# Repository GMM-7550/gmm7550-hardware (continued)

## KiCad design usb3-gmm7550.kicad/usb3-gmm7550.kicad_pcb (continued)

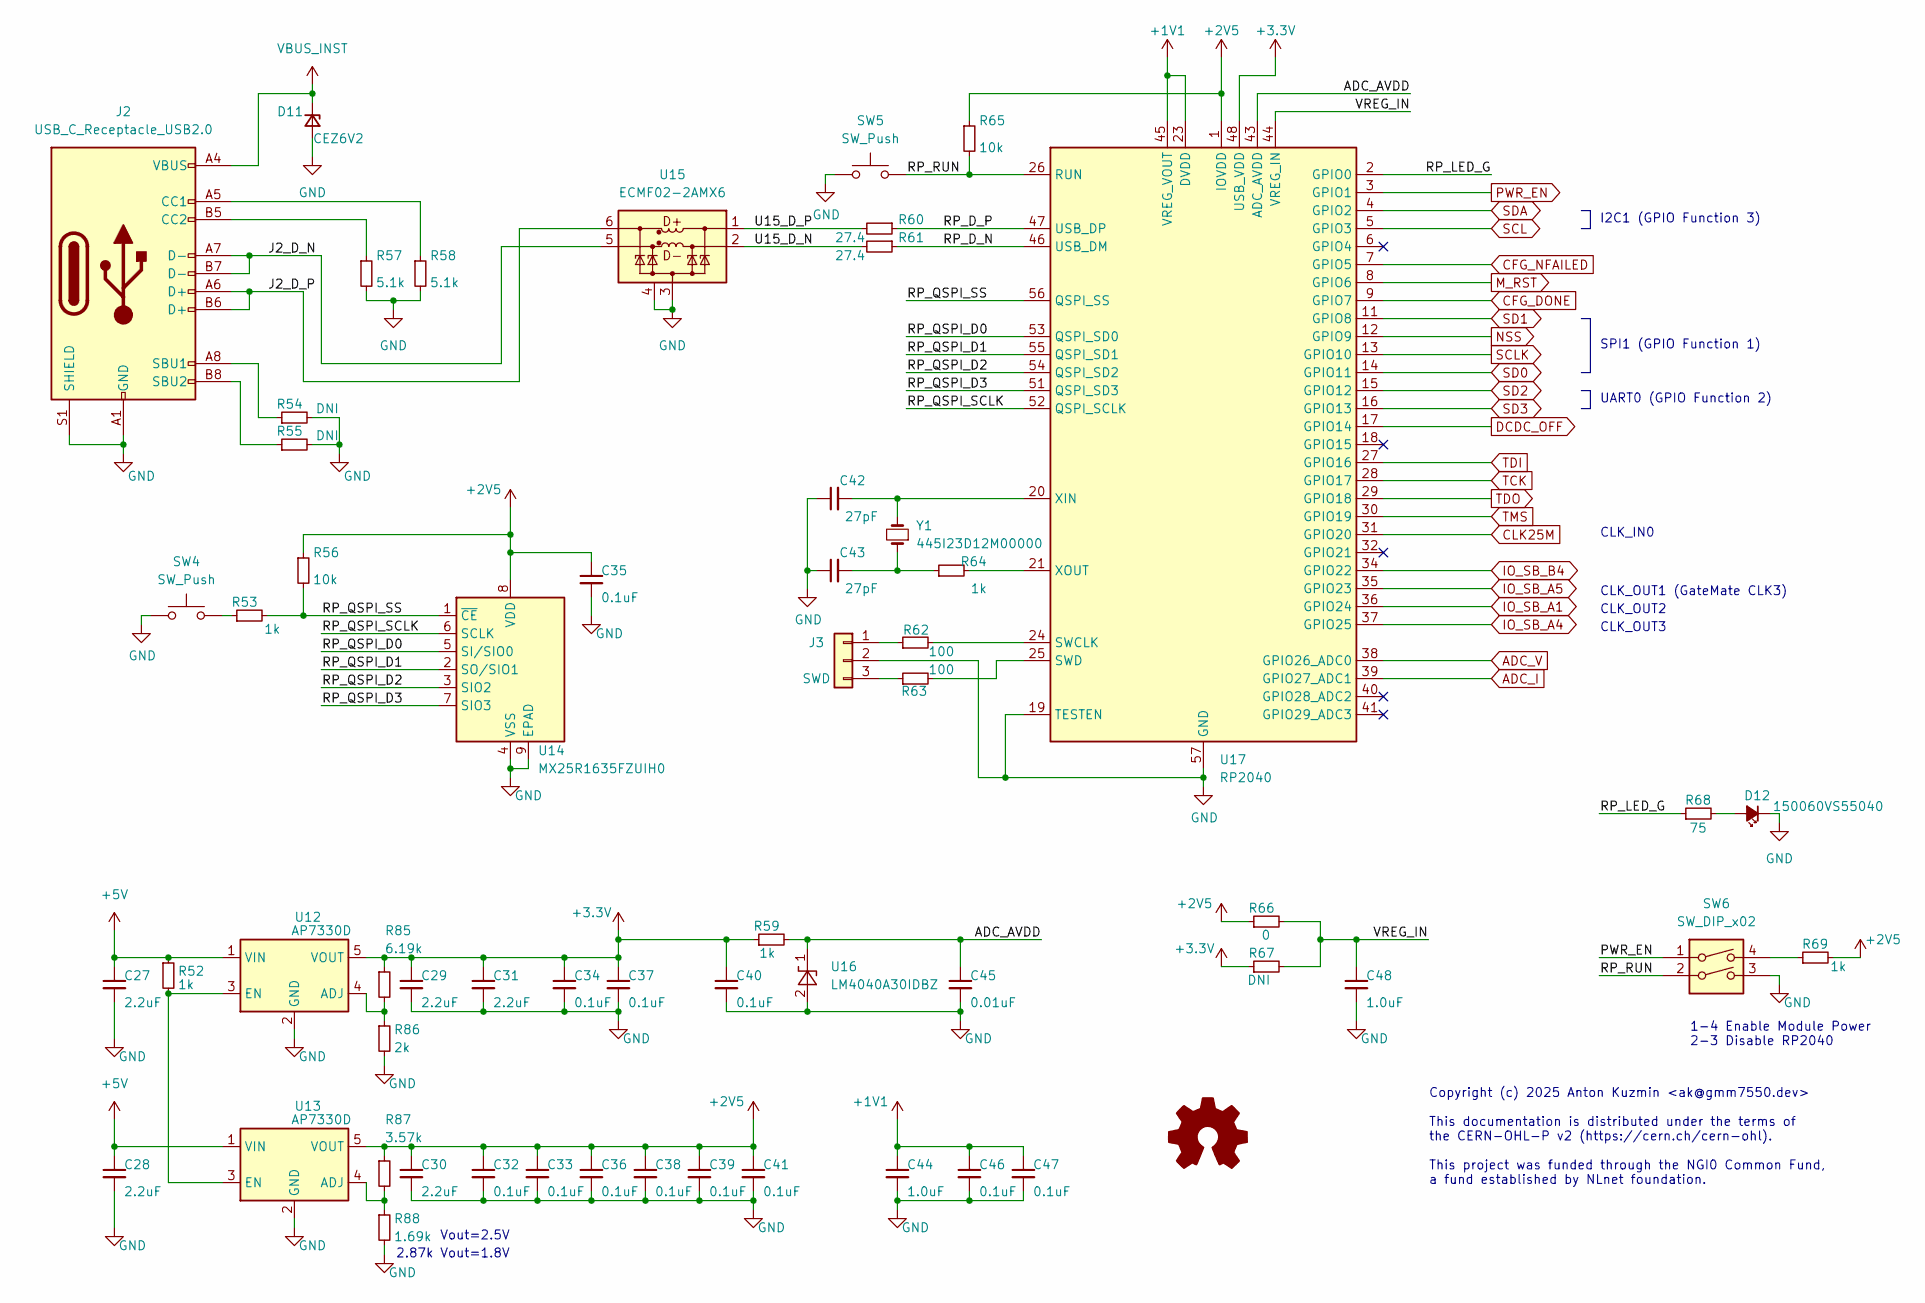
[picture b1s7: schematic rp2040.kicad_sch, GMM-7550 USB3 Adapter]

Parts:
C27, C28, C29, C30, C31: 2.2uF; C_0603_1608Metric
C32, C33, C34, C35, C36, C37, C38, C39, C40, C41, C46, C47: 0.1uF; C_0402_1005Metric
C42, C43: 27pF; C_0402_1005Metric
C44, C48: 1.0uF; C_0402_1005Metric
C45: 0.01uF; C_0402_1005Metric
D11: CEZ6V2; D_SOD-523
D12: 150060VS55040; LED_0603_1608Metric
J2: USB_C_Receptacle_USB2.0; USB_C_Receptacle_GCT_USB4105-xx-A_16P_TopMnt_Horizontal
J3: SWD; JST_SH_SM03B-SRSS-TB_1x03-1MP_P1.00mm_Horizontal
R52, R53, R59, R64, R69: 1k; R_0402_1005Metric
R54, R55, R67: DNI; R_0402_1005Metric
R56, R65: 10k; R_0402_1005Metric
R57, R58: 5.1k; R_0402_1005Metric
R60, R61: 27.4; R_0402_1005Metric
R62, R63: 100; R_0402_1005Metric
R66: 0; R_0402_1005Metric
R68: 75; R_0402_1005Metric
R85: 6.19k; R_0402_1005Metric
R86: 2k; R_0402_1005Metric
R87: 3.57k; R_0402_1005Metric
R88: 1.69k; R_0402_1005Metric
SW4, SW5: SW_Push; SW_SPST_PTS810
SW6: SW_DIP_x02; SW_DIP_SPSTx02_Slide_Omron_A6H-2101_W6.15mm_P1.27mm
U12, U13: AP7330D; SOT-23-5
U14: MX25R1635FZUIH0; Winbond_USON-8-1EP_3x2mm_P0.5mm_EP0.2x1.6mm
U15: ECMF02-2AMX6; ST_UQFN-6L_1.5x1.7mm_P0.5mm
U16: LM4040A30IDBZ; SOT-23
U17: RP2040; QFN-56-1EP_7x7mm_P0.4mm_EP3.2x3.2mm
Y1: 445I23D12M00000; Crystal_SMD_5032-2Pin_5.0x3.2mm

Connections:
+1V1: C44.1, C46.1, C47.1, U17.23 (DVDD), U17.45 (VREG_VOUT), U17.50 (DVDD)
+2V5: C30.1, C32.1, C33.1, C35.1, C36.1, C38.1, C39.1, C41.1, R56.1, R65.1, R66.1, R69.2, R87.1, U13.5 (VOUT), U14.8 (VDD), U17.1 (IOVDD), U17.10 (IOVDD), U17.22 (IOVDD), U17.33 (IOVDD), U17.42 (IOVDD), U17.49 (IOVDD)
+3.3V: C29.1, C31.1, C34.1, C37.1, C40.1, R59.1, R67.1, R85.1, U12.5 (VOUT), U17.48 (USB_VDD); also elsewhere on the board
+5V: C27.1, C28.1, R52.1, U12.1 (VIN), U13.1 (VIN); also elsewhere on the board
/RP2040/ADC_AVDD: C45.1, R59.2, U16.1 (K), U17.43 (ADC_AVDD)
/RP2040/J2_D_N: J2.A7 (D-), J2.B7 (D-), U15.5 (D-_out)
/RP2040/J2_D_P: J2.A6 (D+), J2.B6 (D+), U15.6 (D+_out)
/RP2040/RP_D_N: R61.1, U17.46 (USB_DM)
/RP2040/RP_D_P: R60.1, U17.47 (USB_DP)
/RP2040/RP_LED_G: R68.1, U17.2 (GPIO0)
/RP2040/RP_QSPI_D0: U14.5 (SI/SIO0), U17.53 (QSPI_SD0)
/RP2040/RP_QSPI_D1: U14.2 (SO/SIO1), U17.55 (QSPI_SD1)
/RP2040/RP_QSPI_D2: U14.3 (SIO2), U17.54 (QSPI_SD2)
/RP2040/RP_QSPI_D3: U14.7 (SIO3), U17.51 (QSPI_SD3)
/RP2040/RP_QSPI_SCLK: U14.6 (SCLK), U17.52 (QSPI_SCLK)
/RP2040/RP_QSPI_SS: R53.2, R56.2, U14.1 (~CE), U17.56 (QSPI_SS)
/RP2040/RP_RUN: R65.2, SW5.2, SW6.2, U17.26 (RUN)
/RP2040/U15_D_N: R61.2, U15.2 (D-_in)
/RP2040/U15_D_P: R60.2, U15.1 (D+_in)
/RP2040/VREG_IN: C48.1, R66.2, R67.2, U17.44 (VREG_IN)
ADC_I: U17.39 (GPIO27_ADC1); also elsewhere on the board
ADC_V: U17.38 (GPIO26_ADC0); also elsewhere on the board
CFG_DONE: U17.9 (GPIO7); also elsewhere on the board
CFG_NFAILED: U17.7 (GPIO5); also elsewhere on the board
CLK25M: U17.31 (GPIO20); also elsewhere on the board
DCDC_OFF: U17.17 (GPIO14); also elsewhere on the board
GND: C27.2, C28.2, C29.2, C30.2, C31.2, C32.2, C33.2, C34.2, C35.2, C36.2, C37.2, C38.2, C39.2, C40.2, C41.2, C42.1, C43.1, C44.2, C45.2, C46.2, C47.2, C48.2, D11.2 (A), D12.1 (K), J2.A1 (GND), J2.A12 (GND), J2.B1 (GND), J2.B12 (GND), J2.S1 (SHIELD), J3.2, R54.2, R55.2, R57.2, R58.2, R86.2, R88.2, SW4.1, SW5.1, SW6.3, U12.2 (GND), U13.2 (GND), U14.4 (VSS), U14.9 (EPAD), U15.3 (GND), U15.4 (NC), U16.2 (A), U17.19 (TESTEN), U17.57 (GND); also elsewhere on the board
IO_SB_A1: U17.36 (GPIO24); also elsewhere on the board
IO_SB_A4: U17.37 (GPIO25); also elsewhere on the board
IO_SB_A5: U17.35 (GPIO23); also elsewhere on the board
IO_SB_B4: U17.34 (GPIO22); also elsewhere on the board
M_RST: U17.8 (GPIO6); also elsewhere on the board
NSS: U17.12 (GPIO9); also elsewhere on the board
unnamed: C43.2, R64.1, Y1.1
unnamed: D12.2 (A), R68.2
unnamed: J2.A5 (CC1), R58.1
unnamed: J2.B5 (CC2), R57.1
unnamed: J2.A8 (SBU1), R54.1
unnamed: J2.B8 (SBU2), R55.1
unnamed: J3.1, R62.1
unnamed: J3.3, R63.1
unnamed: R53.1, SW4.2
unnamed: R69.1, SW6.4
unnamed: R85.2, R86.1, U12.4 (ADJ)
unnamed: R52.2, U12.3 (EN), U13.3 (EN)
unnamed: R87.2, R88.1, U13.4 (ADJ)
unnamed: R62.2, U17.24 (SWCLK)
unnamed: R63.2, U17.25 (SWD)
unnamed: C42.2, U17.20 (XIN), Y1.2
unnamed: R64.2, U17.21 (XOUT)
PWR_EN: SW6.1, U17.3 (GPIO1); also elsewhere on the board
SCL: U17.5 (GPIO3); also elsewhere on the board
SCLK: U17.13 (GPIO10); also elsewhere on the board
SD0: U17.14 (GPIO11); also elsewhere on the board
SD1: U17.11 (GPIO8); also elsewhere on the board
SD2: U17.15 (GPIO12); also elsewhere on the board
SD3: U17.16 (GPIO13); also elsewhere on the board
SDA: U17.4 (GPIO2); also elsewhere on the board
TCK: U17.28 (GPIO17); also elsewhere on the board
TDI: U17.27 (GPIO16); also elsewhere on the board
TDO: U17.29 (GPIO18); also elsewhere on the board
TMS: U17.30 (GPIO19); also elsewhere on the board
VBUS_INST: D11.1 (K), J2.A4 (VBUS), J2.A9 (VBUS), J2.B4 (VBUS), J2.B9 (VBUS); also elsewhere on the board

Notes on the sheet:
CLK_IN0
CLK_OUT1 (GateMate CLK3)
I2C1 (GPIO Function 3)
Vout=2.5V
2.87k Vout=1.8V
Copyright (c) 2025 Anton Kuzmin <ak@gmm7550.dev> This documentation is distributed under the terms of the CERN-OHL-P v2 (https://cern.ch/cern-ohl). This project was funded through the NGI0 Common Fund, a fund established by NLnet foundation.
CLK_OUT3
UART0 (GPIO Function 2)
1-4 Enable Module Power 2-3 Disable RP2040
CLK_OUT2
SPI1 (GPIO Function 1)

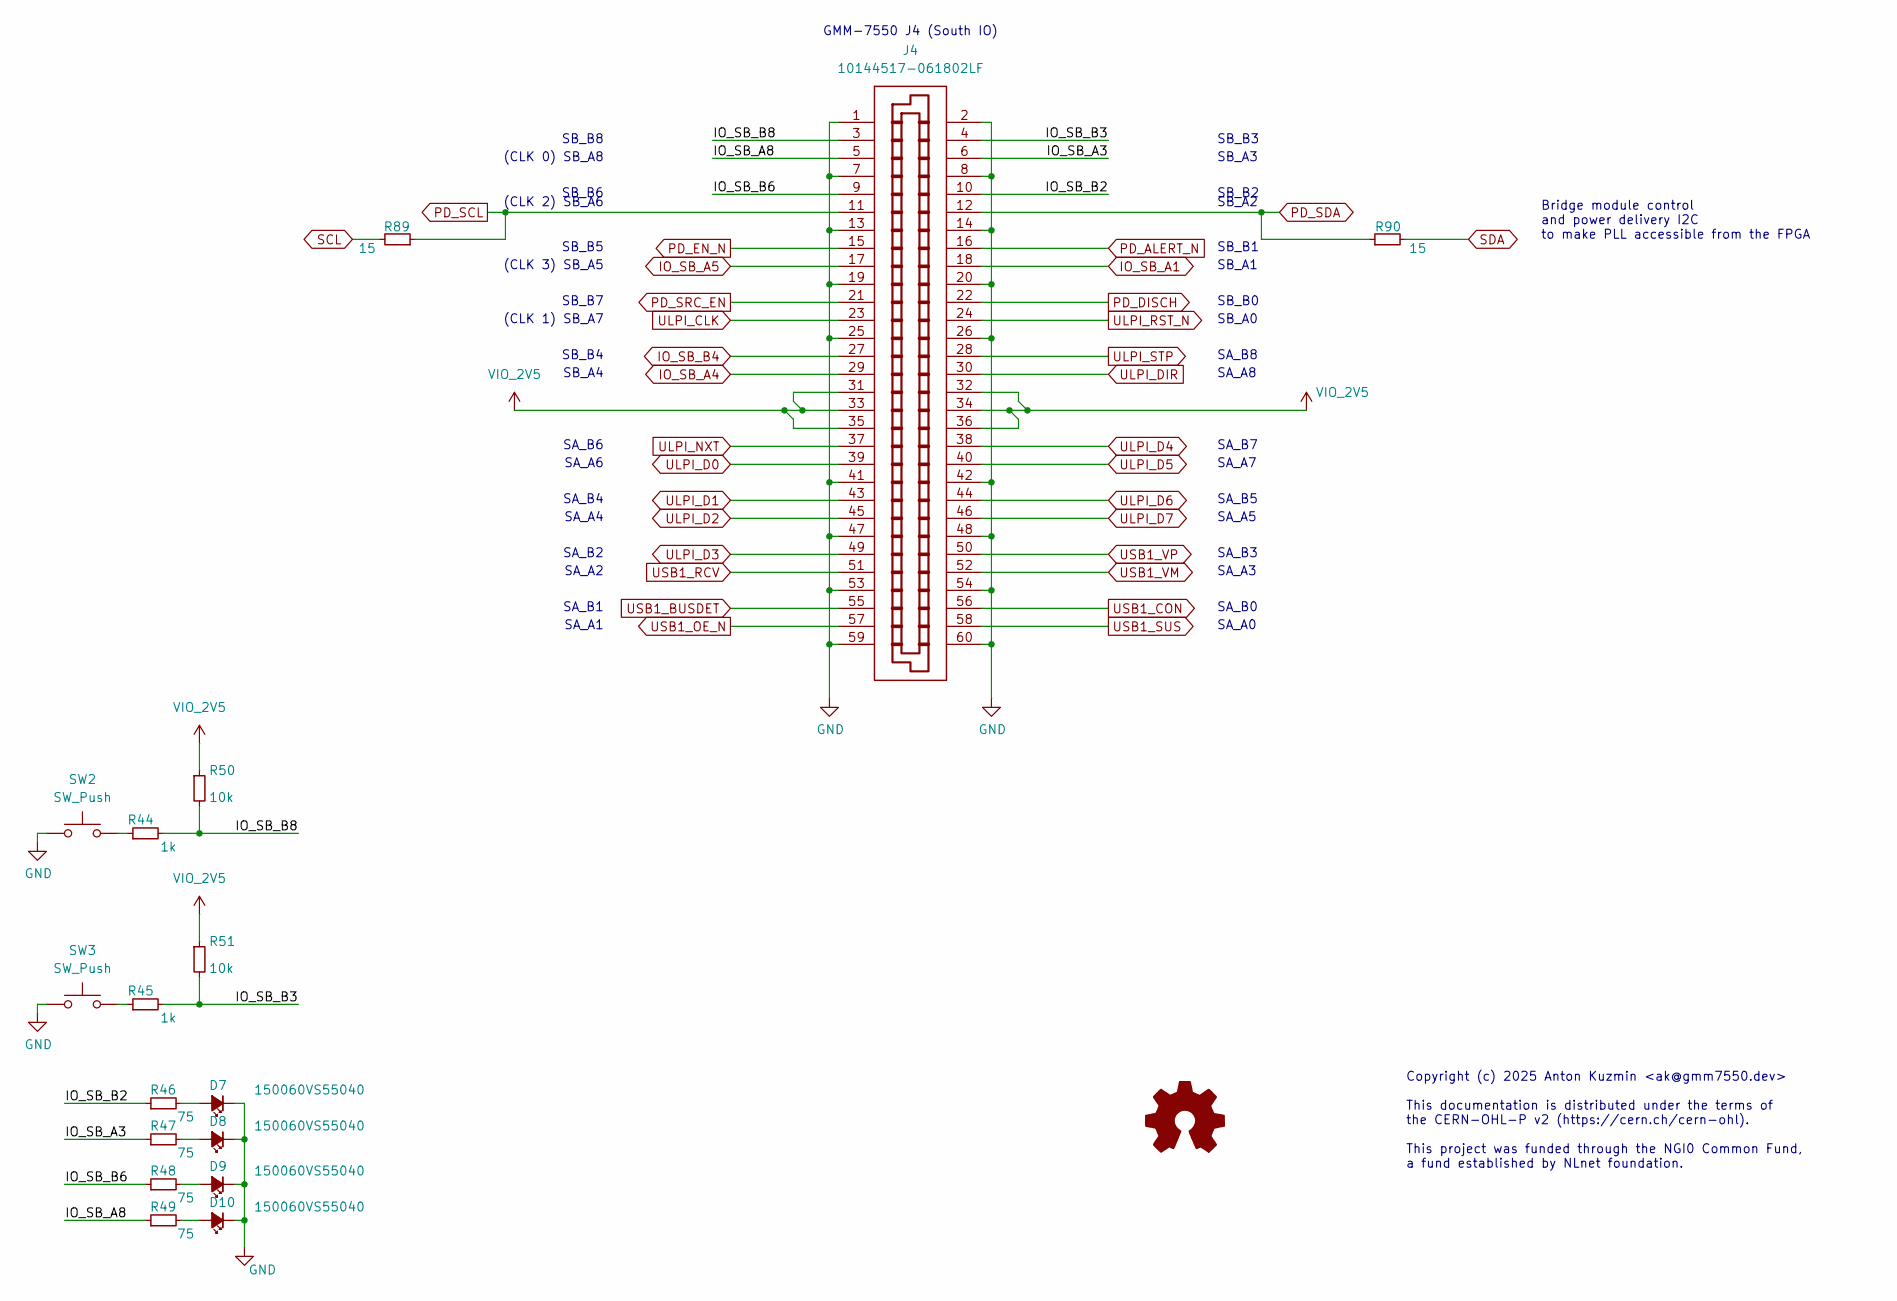
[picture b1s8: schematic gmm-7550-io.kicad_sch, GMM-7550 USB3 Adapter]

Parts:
D7, D8, D9, D10: 150060VS55040; LED_0603_1608Metric
J4: 10144517-061802LF
R44, R45: 1k; R_0402_1005Metric
R46, R47, R48, R49: 75; R_0402_1005Metric
R50, R51: 10k; R_0402_1005Metric
R89, R90: 15; R_0402_1005Metric
SW2, SW3: SW_Push; SW_SPST_PTS810

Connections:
/GMM-7550 IO/IO_SB_A3: J4.6, R47.1
/GMM-7550 IO/IO_SB_A8: J4.5, R49.1
/GMM-7550 IO/IO_SB_B2: J4.10, R46.1
/GMM-7550 IO/IO_SB_B3: J4.4, R45.2, R51.2
/GMM-7550 IO/IO_SB_B6: J4.9, R48.1
/GMM-7550 IO/IO_SB_B8: J4.3, R44.2, R50.2
GND: D7.1 (K), D8.1 (K), D9.1 (K), D10.1 (K), J4.1, J4.2, J4.7, J4.8, J4.13, J4.14, J4.19, J4.20, J4.25, J4.26, J4.41, J4.42, J4.47, J4.48, J4.53, J4.54, J4.59, J4.60, SW2.1, SW3.1; also elsewhere on the board
IO_SB_A1: J4.18; also elsewhere on the board
IO_SB_A4: J4.29; also elsewhere on the board
IO_SB_A5: J4.17; also elsewhere on the board
IO_SB_B4: J4.27; also elsewhere on the board
unnamed: D7.2 (A), R46.2
unnamed: D8.2 (A), R47.2
unnamed: D9.2 (A), R48.2
unnamed: D10.2 (A), R49.2
unnamed: R44.1, SW2.2
unnamed: R45.1, SW3.2
PD_ALERT_N: J4.16; also elsewhere on the board
PD_DISCH: J4.22; also elsewhere on the board
PD_EN_N: J4.15; also elsewhere on the board
PD_SCL: J4.11, R89.1; also elsewhere on the board
PD_SDA: J4.12, R90.1; also elsewhere on the board
PD_SRC_EN: J4.21; also elsewhere on the board
SCL: R89.2; also elsewhere on the board
SDA: R90.2; also elsewhere on the board
ULPI_CLK: J4.23; also elsewhere on the board
ULPI_D0: J4.39; also elsewhere on the board
ULPI_D1: J4.43; also elsewhere on the board
ULPI_D2: J4.45; also elsewhere on the board
ULPI_D3: J4.49; also elsewhere on the board
ULPI_D4: J4.38; also elsewhere on the board
ULPI_D5: J4.40; also elsewhere on the board
ULPI_D6: J4.44; also elsewhere on the board
ULPI_D7: J4.46; also elsewhere on the board
ULPI_DIR: J4.30; also elsewhere on the board
ULPI_NXT: J4.37; also elsewhere on the board
ULPI_RST_N: J4.24; also elsewhere on the board
ULPI_STP: J4.28; also elsewhere on the board
USB1_BUSDET: J4.55; also elsewhere on the board
USB1_CON: J4.56; also elsewhere on the board
USB1_OE_N: J4.57; also elsewhere on the board
USB1_RCV: J4.51; also elsewhere on the board
USB1_SUS: J4.58; also elsewhere on the board
USB1_VM: J4.52; also elsewhere on the board
USB1_VP: J4.50; also elsewhere on the board
VIO_2V5: J4.31, J4.32, J4.33, J4.34, J4.35, J4.36, R50.1, R51.1; also elsewhere on the board

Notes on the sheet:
SB_B7
SA_A0
SA_B8
(CLK 2) SB_A6
SA_B1
SA_A8
SA_A6
SA_A2
SB_B5
(CLK 0) SB_A8
SB_A0
GMM-7550 J4 (South IO)
SA_A7
SB_B0
SB_B3
SB_B4
SA_B7
SB_B2
(CLK 1) SB_A7
SA_A5
SB_B1
SB_A1
SA_B3
SB_A2
SB_B8
SA_B6
Bridge module control and power delivery I2C to make PLL accessible from the FPGA
SA_B5
SB_A3
(CLK 3) SB_A5
Copyright (c) 2025 Anton Kuzmin <ak@gmm7550.dev> This documentation is distributed under the terms of the CERN-OHL-P v2 (https://cern.ch/cern-ohl). This project was funded through the NGI0 Common Fund, a fund established by NLnet foundation.
SA_A3
SB_B6
SA_B2
SA_A1
SA_B4
SB_A4
SA_B0
SA_A4

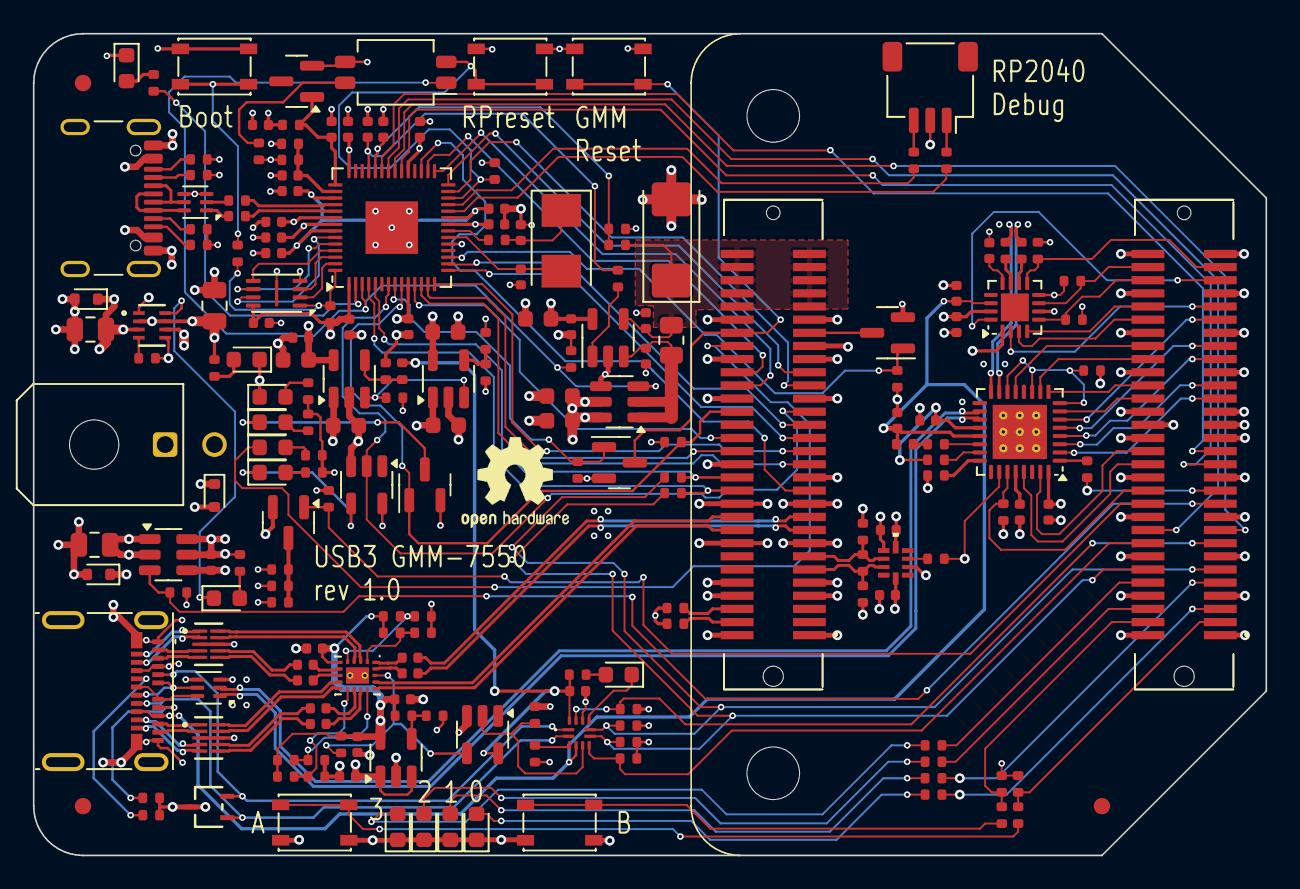
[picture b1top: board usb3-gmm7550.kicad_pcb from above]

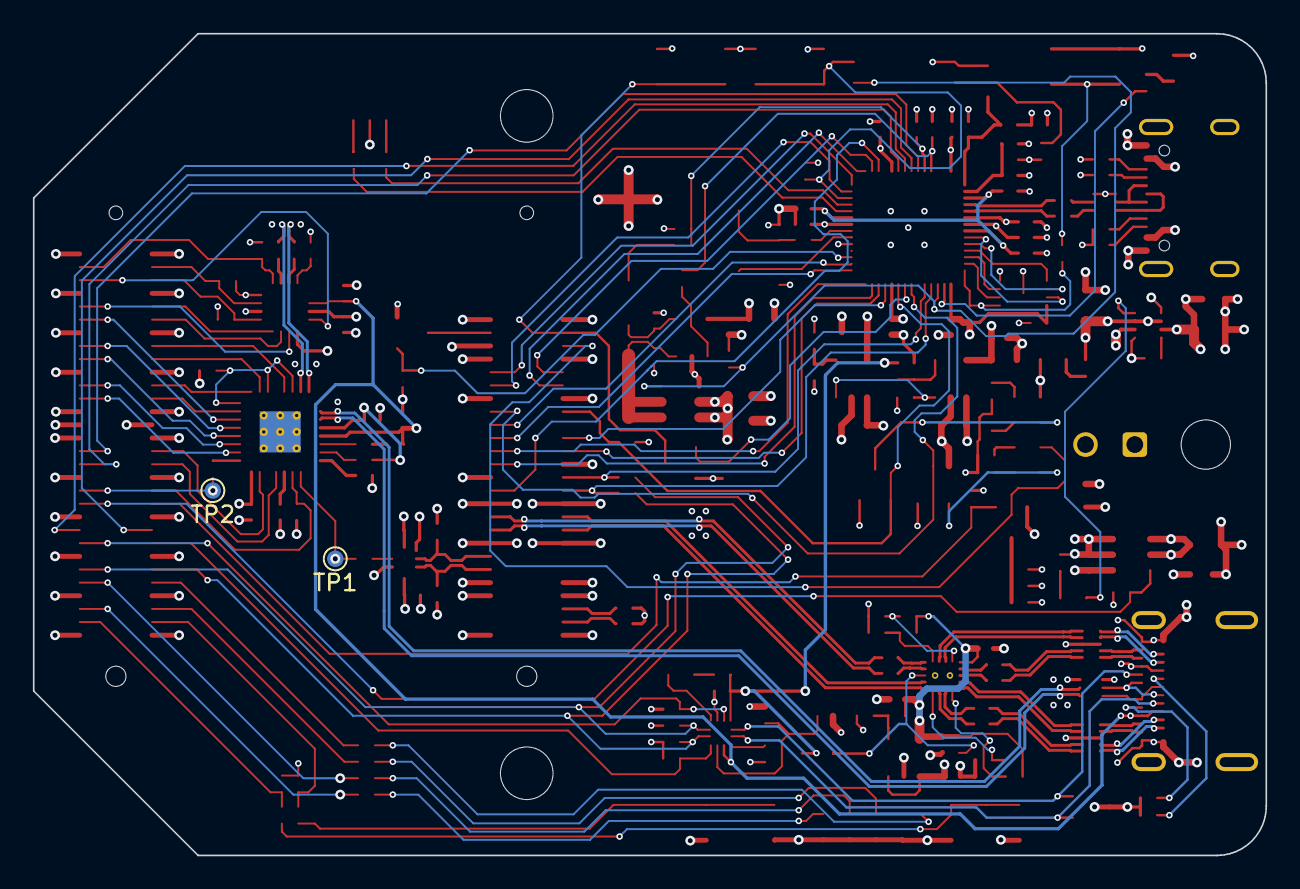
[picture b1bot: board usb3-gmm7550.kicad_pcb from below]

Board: 4 copper layers, 75.0 x 50.0 mm, 205 parts (2 on the bottom side), 184 nets.

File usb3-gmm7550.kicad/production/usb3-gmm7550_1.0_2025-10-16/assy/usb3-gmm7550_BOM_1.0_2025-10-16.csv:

"Reference","Qty","Value","DNP","Exclude from BOM","Exclude from Board","Footprint","Datasheet"
"C1,C4,C5,C6,C7,C8,C9,C10,C12,C14,C15,C16,C21,C22,C26,C32,C33,C34,C35,C36,C37,C38,C39,C40,C41,C46,C47","27","0.1uF","","","","Capacitor_SMD:C_0402_1005Metric","~"
"C2,C3,C13,C17,C18,C44,C48,C49,C53","9","1.0uF","","","","Capacitor_SMD:C_0402_1005Metric","~"
"C11,C23,C45,C56","4","0.01uF","","","","Capacitor_SMD:C_0402_1005Metric","~"
"C19,C20,C27,C28,C29,C30,C31","7","2.2uF","","","","Capacitor_SMD:C_0603_1608Metric","~"
"C24","1","DNI","","","","Capacitor_SMD:C_0402_1005Metric","~"
"C25","1","47uF, 16V","","","","Capacitor_Tantalum_SMD:CP_EIA-6032-28_Kemet-C","~"
"C42,C43","2","27pF","","","","Capacitor_SMD:C_0402_1005Metric","~"
"C50,C51,C52","3","10uF","","","","Capacitor_SMD:C_0805_2012Metric","~"
"D1,D11,D14","3","CEZ6V2","","","","Diode_SMD:D_SOD-523","~"
"D2","1","ESD752DCKR","","","","usb3-gmm7550:SOT-SC70_DCK_TEX","https://www.ti.com/lit/gpn/esd752"
"D3,D4,D7,D8,D9,D10,D12,D13,D16","9","150060VS55040","","","","LED_SMD:LED_0603_1608Metric","~"
"D5,D15","2","HSMA-C197","","","","LED_SMD:LED_0603_1608Metric","~"
"D6","1","HSMC-C197","","","","LED_SMD:LED_0603_1608Metric","~"
"J1","1","USB_C_Receptacle","","","","Connector_USB:USB_C_Receptacle_Molex_105450-0101","https://www.usb.org/sites/default/files/documents/usb_type-c.zip"
"J2","1","USB_C_Receptacle_USB2.0","","","","Connector_USB:USB_C_Receptacle_GCT_USB4105-xx-A_16P_TopMnt_Horizontal","https://www.usb.org/sites/default/files/documents/usb_type-c.zip"
"J3","1","SWD","","","","Connector_JST:JST_SH_SM03B-SRSS-TB_1x03-1MP_P1.00mm_Horizontal","~"
"J4,J5","2","10144517-061802LF","","","","Amphenol:10144517-061802LF",""
"J6","1","DNI","","","","Connector_Molex:Molex_Micro-Fit_3.0_43045-0200_2x01_P3.00mm_Horizontal","~"
"Q1,Q2,Q3,Q4","4","NX6008NBK","","","","Package_TO_SOT_SMD:SOT-23","~"
"R1,R2,R5,R6,R7,R8,R9,R10,R11,R12,R54,R55,R67,R79","14","DNI","","","","Resistor_SMD:R_0402_1005Metric","~"
"R3,R13,R20,R21,R23,R26,R29,R31,R32,R34,R35,R42,R43,R50,R51,R56,R65,R70,R71,R72,R76,R77,R78","23","10k","","","","Resistor_SMD:R_0402_1005Metric","~"
"R4,R24","2","8.06k","","","","Resistor_SMD:R_0402_1005Metric","~"
"R14,R16,R57,R58","4","5.1k","","","","Resistor_SMD:R_0402_1005Metric","~"
"R15,R36,R40,R62,R63,R83","6","100","","","","Resistor_SMD:R_0402_1005Metric","~"
"R17,R28,R60,R61","4","27.4","","","","Resistor_SMD:R_0402_1005Metric","~"
"R18,R19,R89,R90","4","15","","","","Resistor_SMD:R_0402_1005Metric","~"
"R22,R66,R80","3","0","","","","Resistor_SMD:R_0402_1005Metric","~"
"R25,R27,R44,R45,R52,R53,R59,R64,R69,R73,R74,R75","12","1k","","","","Resistor_SMD:R_0402_1005Metric","~"
"R30,R33,R41,R46,R47,R48,R49,R68","8","75","","","","Resistor_SMD:R_0402_1005Metric","~"
"R37","1","0.02","","","","Resistor_SMD:R_0805_2012Metric","~"
"R38","1","120k","","","","Resistor_SMD:R_0402_1005Metric","~"
"R39","1","100k","","","","Resistor_SMD:R_0402_1005Metric","~"
"R81","1","900k","","","","Resistor_SMD:R_0402_1005Metric","~"
"R82,R84","2","301","","","","Resistor_SMD:R_0402_1005Metric","~"
"R85","1","6.19k","","","","Resistor_SMD:R_0402_1005Metric","~"
"R86","1","2k","","","","Resistor_SMD:R_0402_1005Metric","~"
"R87","1","3.57k","","","","Resistor_SMD:R_0402_1005Metric","~"
"R88","1","1.69k","","","","Resistor_SMD:R_0402_1005Metric","~"
"SW1,SW2,SW3,SW4,SW5","5","SW_Push","","","","Button_Switch_SMD:SW_SPST_PTS810","~"
"SW6","1","SW_DIP_x02","","","","Button_Switch_SMD:SW_DIP_SPSTx02_Slide_Omron_A6H-2101_W6.15mm_P1.27mm","~"
"U1,U2","2","ECMF4-40A100N10","","","","usb3-gmm7550:UQFN10L_1P4X2P25X0P4_STM","https://www.st.com/resource/en/datasheet/ecmf4-40a100n10.pdf"
"U3,U15","2","ECMF02-2AMX6","","","","Package_DFN_QFN:ST_UQFN-6L_1.5x1.7mm_P0.5mm","https://www.st.com/resource/en/datasheet/ecmf02-2amx6.pdf"
"U4,U12,U13","3","AP7330D","","","","Package_TO_SOT_SMD:SOT-23-5",""
"U5","1","TUSB542","","","","usb3-gmm7550:Texas_X2QFN-18-1EP_2x2.4mm_P0.4mm_EP1x1.4mm_ThermalVias",""
"U6","1","SN65LVDS4RSER","","","","usb3-gmm7550:RSE10","https://www.ti.com/lit/gpn/sn65lvds4"
"U7","1","USB3340","","","","Package_DFN_QFN:QFN-32-1EP_5x5mm_P0.5mm_EP3.3x3.3mm_ThermalVias","https://ww1.microchip.com/downloads/aemDocuments/documents/U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"
"U8","1","STUSB03E","","","","Package_DFN_QFN:QFN-16-1EP_3x3mm_P0.5mm_EP1.7x1.7mm","https://www.st.com/resource/en/datasheet/stusb03e.pdf"
"U9","1","SiP32510","","","","Package_TO_SOT_SMD:SOT-23-6","https://www.vishay.com/docs/63577/sip32510.pdf"
"U10","1","SN74LVC1G07DBV","","","","Package_TO_SOT_SMD:SOT-23-5",""
"U11","1","INA180A2","","","","Package_TO_SOT_SMD:SOT-23-5","http://www.ti.com/lit/ds/symlink/ina180.pdf"
"U14","1","MX25R1635FZUIH0","","","","Package_SON:Winbond_USON-8-1EP_3x2mm_P0.5mm_EP0.2x1.6mm","https://www.mouser.com/datasheet/2/1127/APM_PSRAM_QSPI_APS16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"
"U16","1","LM4040A30IDBZ","","","","Package_TO_SOT_SMD:SOT-23","http://www.ti.com/lit/ds/symlink/lm4040-n.pdf"
"U17","1","RP2040","","","","Package_DFN_QFN:QFN-56-1EP_7x7mm_P0.4mm_EP3.2x3.2mm","https://datasheets.raspberrypi.com/rp2040/rp2040-datasheet.pdf"
"U18","1","FUSB303BTMX","","","","usb3-gmm7550:OnSemi_X2QFN-12_1.6x1.6mm","https://www.onsemi.com/pub/Collateral/FUSB303B-D.PDF"
"U19","1","SiP32508DT","","","","Package_TO_SOT_SMD:TSOT-23-6","https://www.vishay.com/docs/62754/sip32508.pdf"
"U20","1","LM66200DRLR","","","","usb3-gmm7550:SOT-5X3_DRL_TEX","https://www.ti.com/lit/gpn/lm66200"
"U21","1","SN74LVC1G06DBV","","","","Package_TO_SOT_SMD:SOT-23-5","http://www.ti.com/lit/sg/scyt129e/scyt129e.pdf"
"Y1","1","445I23D12M00000","","","","Crystal:Crystal_SMD_5032-2Pin_5.0x3.2mm","~"

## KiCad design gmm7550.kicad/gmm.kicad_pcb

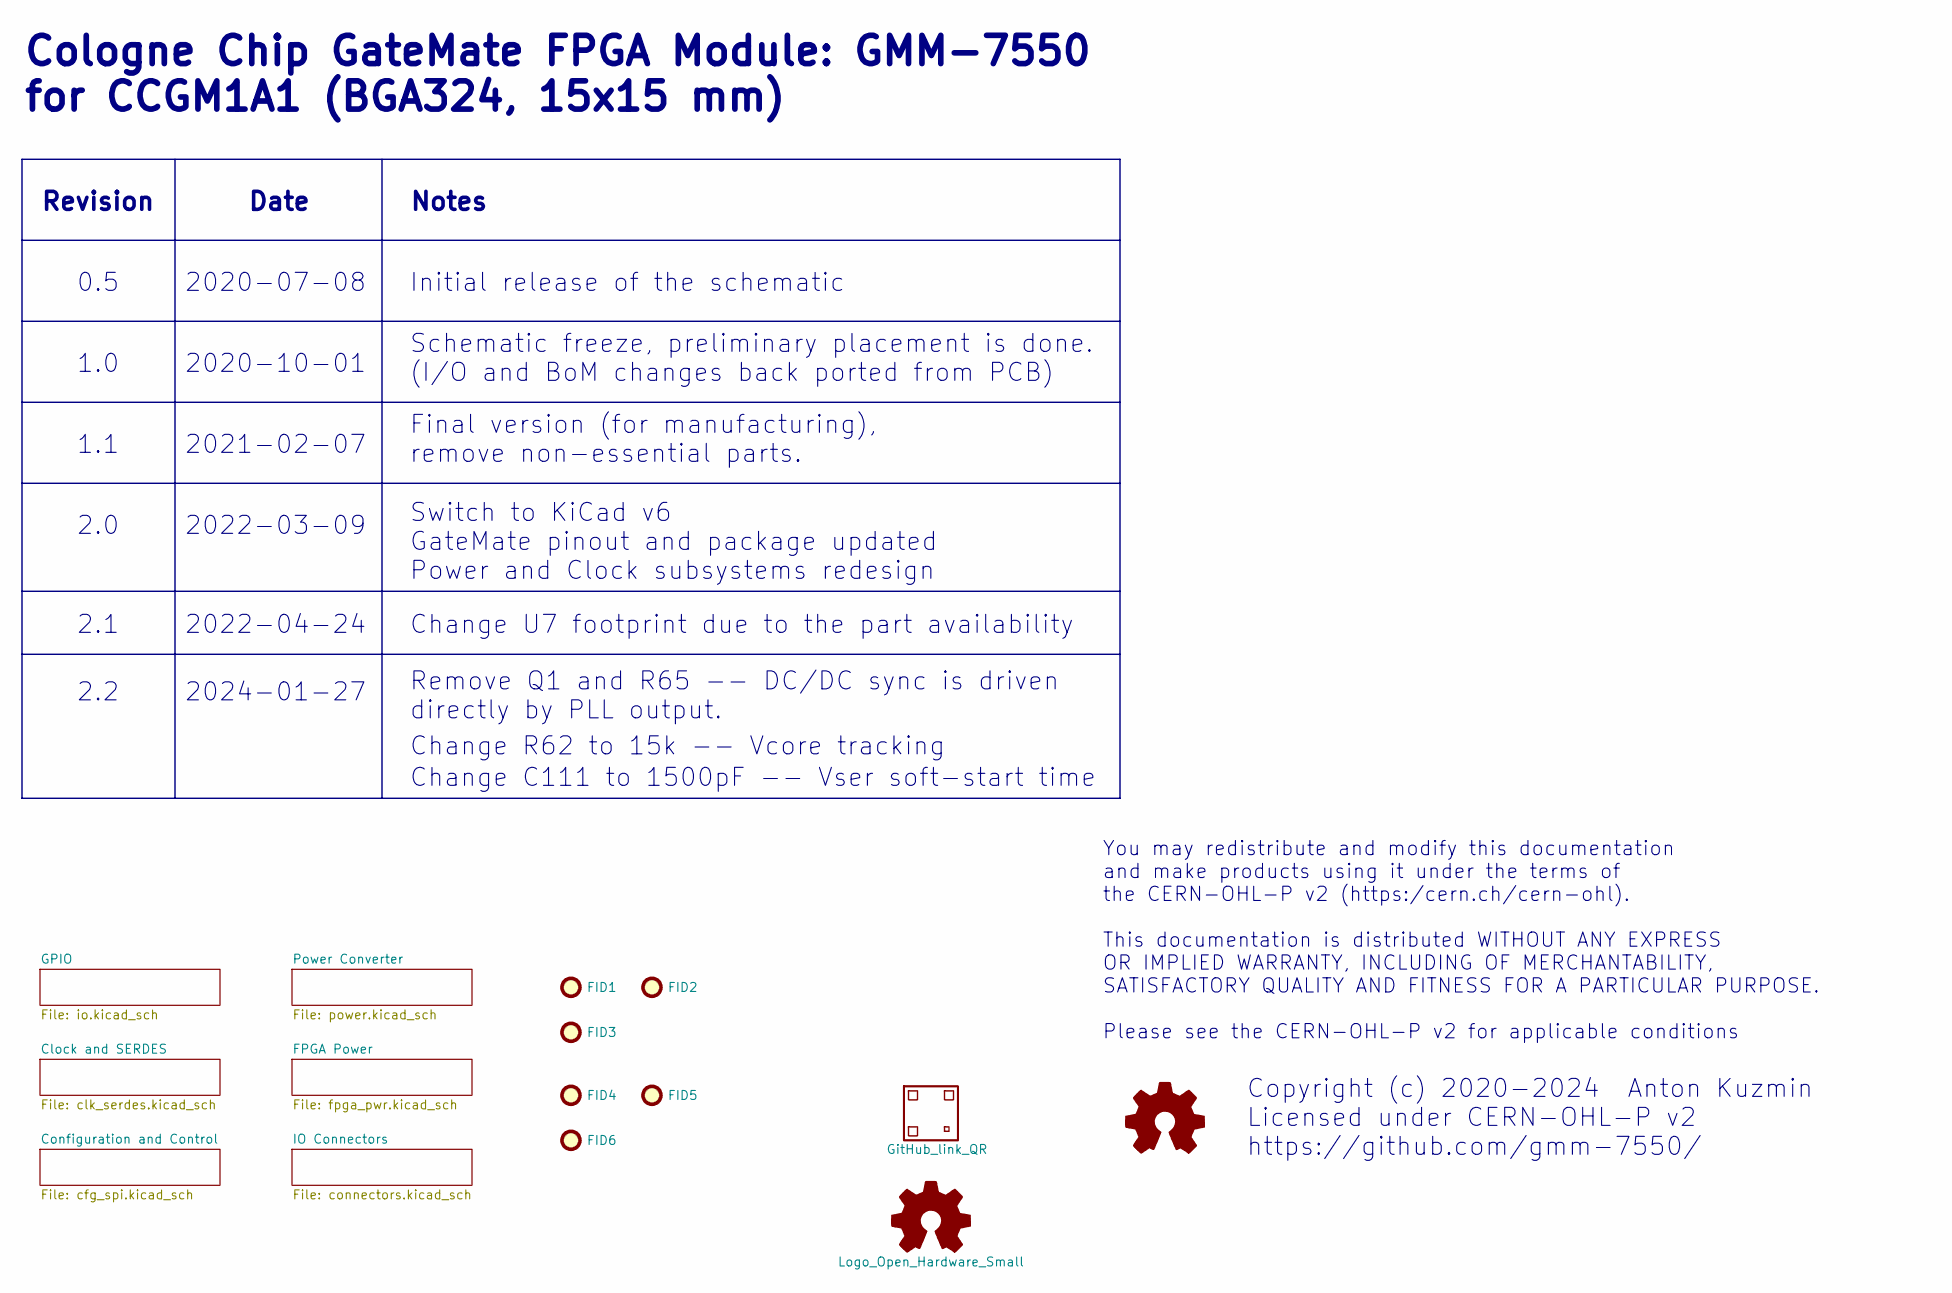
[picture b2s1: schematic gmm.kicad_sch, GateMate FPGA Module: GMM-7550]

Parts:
FID1, FID2, FID3, FID4, FID5, FID6: Fiducial; Fiducial_0.75mm_Mask1.5mm
LOGO1: Logo_Open_Hardware_Small; OSHW-Logo2_7.3x6mm_SilkScreen
QR1: GitHub_link_QR; gmm7550_dev_link_QR

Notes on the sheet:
Revision
Initial release of the schematic
1.1
0.5
Change C111 to 1500pF -- Vser soft-start time
2020-07-08
Final version (for manufacturing), remove non-essential parts.
2022-04-24
Notes
You may redistribute and modify this documentation and make products using it under the terms of the CERN-OHL-P v2 (https:/cern.ch/cern-ohl). This documentation is distributed WITHOUT ANY EXPRESS OR IMPLIED WARRANTY, INCLUDING OF MERCHANTABILITY, SATISFACTORY QUALITY AND FITNESS FOR A PARTICULAR PU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
2020-10-01
2021-02-07
Change R62 to 15k -- Vcore tracking
Copyright (c) 2020-2024 Anton Kuzmin Licensed under CERN-OHL-P v2 https://github.com/gmm-7550/
Switch to KiCad v6 GateMate pinout and package updated Power and Clock subsystems redesign
2.2
Change U7 footprint due to the part availability
Cologne Chip GateMate FPGA Module: GMM-7550 for CCGM1A1 (BGA324, 15x15 mm)
2.1
2.0
2022-03-09
1.0
Remove Q1 and R65 -- DC/DC sync is driven directly by PLL output.
Schematic freeze, preliminary placement is done. (I/O and BoM changes back ported from PCB)
2024-01-27
Date

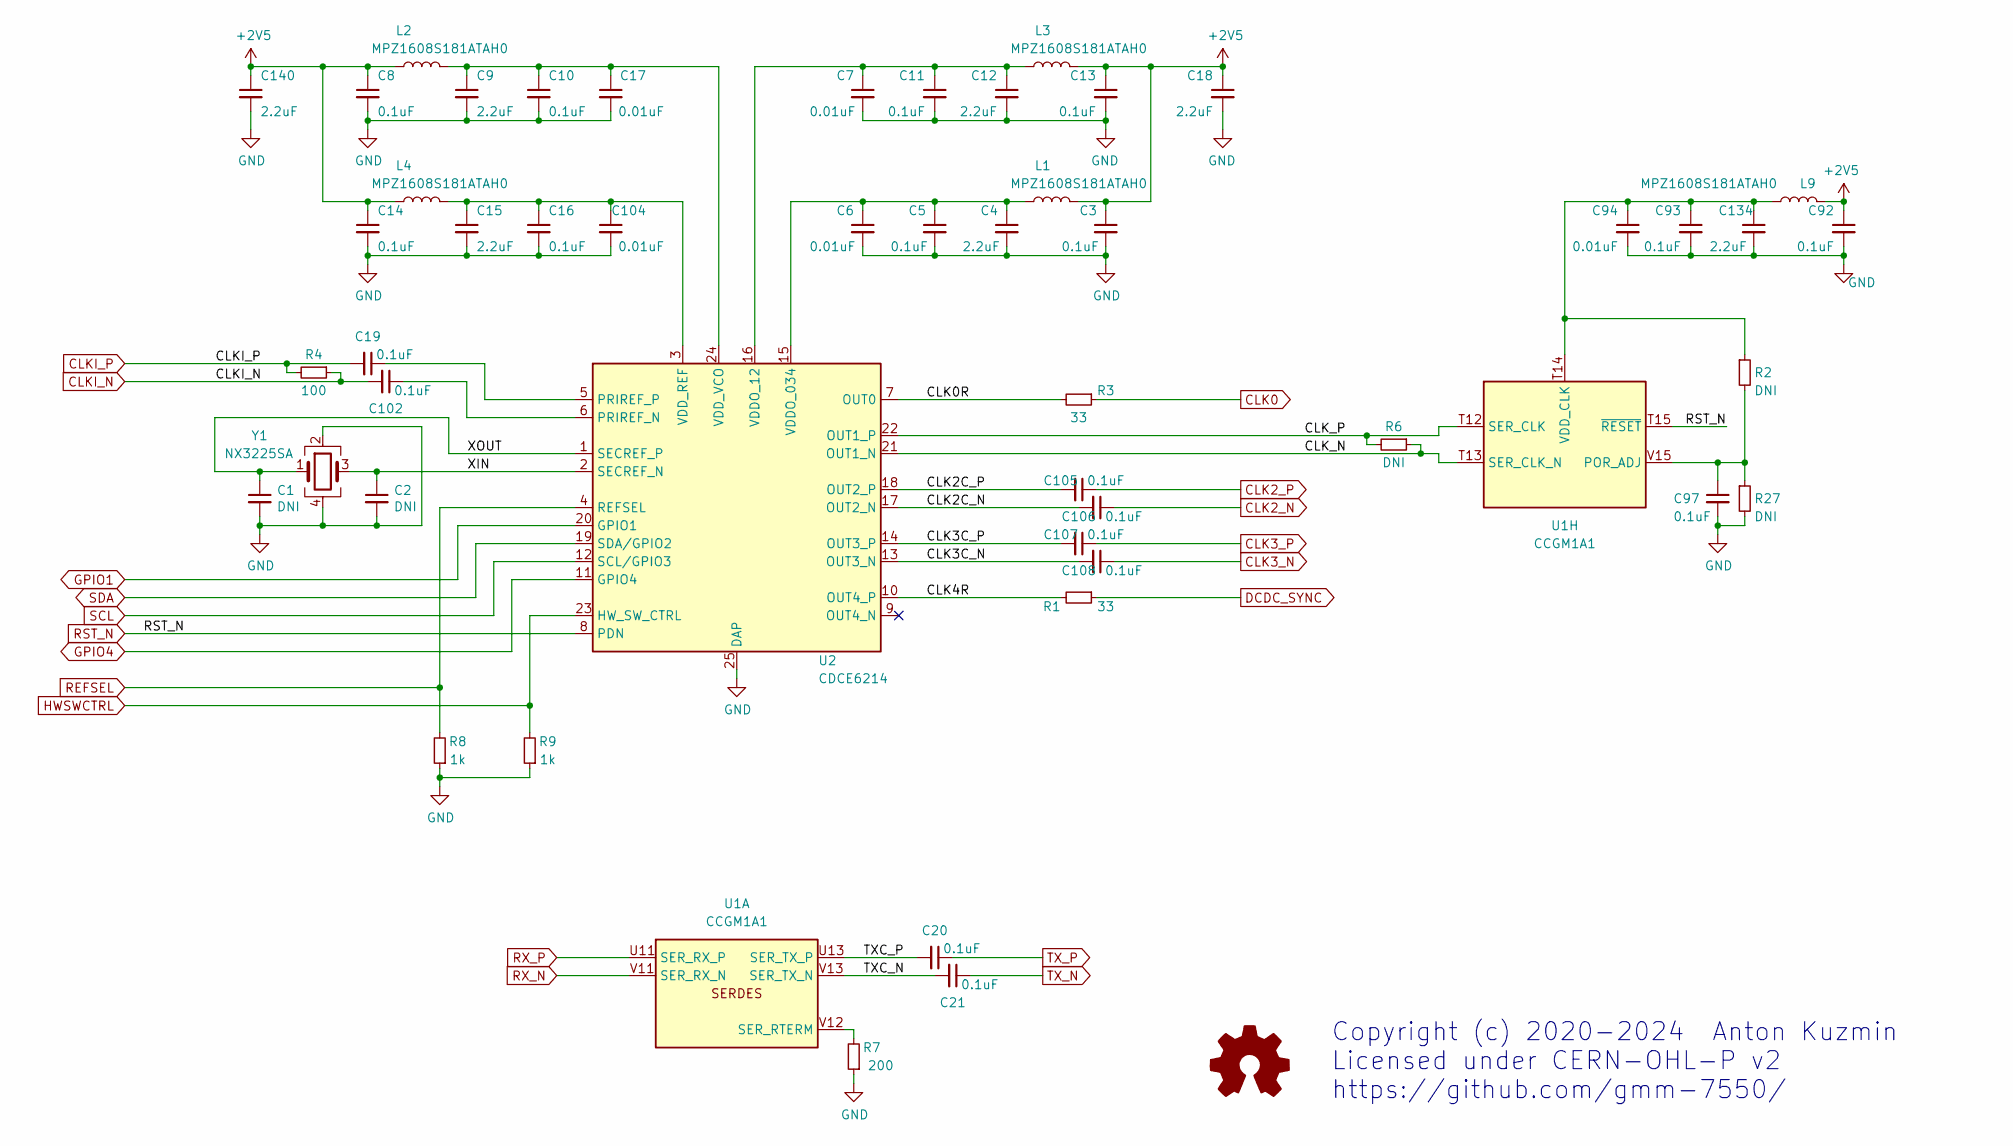
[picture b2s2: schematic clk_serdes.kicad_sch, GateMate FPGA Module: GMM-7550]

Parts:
C1, C2: DNI; C_0402_1005Metric
C3, C5, C8, C10, C11, C13, C14, C16, C19, C20, C21, C92, C93, C97, C102, C105, C106, C107, C108: 0.1uF; C_0402_1005Metric
C4, C9, C12, C15, C18, C134, C140: 2.2uF; C_0603_1608Metric
C6, C7, C17, C94, C104: 0.01uF; C_0402_1005Metric
L1, L2, L3, L4, L9: MPZ1608S181ATAH0; L_0603_1608Metric
R1, R3: 33; R_0402_1005Metric
R2, R6, R27: DNI; R_0402_1005Metric
R4: 100; R_0402_1005Metric
R7: 200; R_0402_1005Metric
R8, R9: 1k; R_0402_1005Metric
U1: CCGM1A1; BGA-324_15.0x15.0mm_Layout18x18_P0.8mm_Ball0.45mm_Pad0.35mm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
U2: CDCE6214; Texas_RGE0024H_EP2.7x2.7mm_ThermalVias
Y1: NX3225SA; Crystal_SMD_3225-4Pin_3.2x2.5mm

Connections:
+2V5: C3.1, C8.1, C13.1, C14.1, C18.1, C92.1, C140.1, L1.2, L2.1, L3.1, L4.1, L9.2; also elsewhere on the board
/Clock and SERDES/CLK0R: R3.2, U2.7 (OUT0)
/Clock and SERDES/CLK2C_N: C107.2, U2.17 (OUT2_N)
/Clock and SERDES/CLK2C_P: C105.2, U2.18 (OUT2_P)
/Clock and SERDES/CLK3C_N: C108.2, U2.13 (OUT3_N)
/Clock and SERDES/CLK3C_P: C106.2, U2.14 (OUT3_P)
/Clock and SERDES/CLK4R: R1.2, U2.10 (OUT4_P)
/Clock and SERDES/CLK_N: R6.1, U1.T13 (SER_CLK_N), U2.21 (OUT1_N)
/Clock and SERDES/CLK_P: R6.2, U1.T12 (SER_CLK), U2.22 (OUT1_P)
/Clock and SERDES/TXC_N: C21.2, U1.V13 (SER_TX_N)
/Clock and SERDES/TXC_P: C20.2, U1.U13 (SER_TX_P)
/Clock and SERDES/XIN: C2.1, U2.2 (SECREF_N), Y1.3
/Clock and SERDES/XOUT: C1.1, U2.1 (SECREF_P), Y1.1
CLK0: R3.1; also elsewhere on the board
CLK2_N: C107.1; also elsewhere on the board
CLK2_P: C105.1; also elsewhere on the board
CLK3_N: C108.1; also elsewhere on the board
CLK3_P: C106.1; also elsewhere on the board
CLKI_N: C102.2, R4.1; also elsewhere on the board
CLKI_P: C19.2, R4.2; also elsewhere on the board
DCDC_SYNC: R1.1; also elsewhere on the board
GND: C1.2, C2.2, C3.2, C4.2, C5.2, C6.2, C7.2, C8.2, C9.2, C10.2, C11.2, C12.2, C13.2, C14.2, C15.2, C16.2, C17.2, C18.2, C92.2, C93.2, C94.2, C97.2, C104.2, C134.2, C140.2, R7.1, R8.1, R9.1, R27.2, U2.25 (DAP), Y1.2, Y1.4; also elsewhere on the board
GPIO1: U2.20 (GPIO1); also elsewhere on the board
GPIO4: U2.11 (GPIO4); also elsewhere on the board
HWSWCTRL: R9.2, U2.23 (HW_SW_CTRL); also elsewhere on the board
unnamed: R7.2, U1.V12 (SER_RTERM)
unnamed: C97.1, R2.2, R27.1, U1.V15 (POR_ADJ)
unnamed: C93.1, C94.1, C134.1, L9.1, R2.1, U1.T14 (VDD_CLK)
unnamed: C102.1, U2.6 (PRIREF_N)
unnamed: C19.1, U2.5 (PRIREF_P)
unnamed: C7.1, C11.1, C12.1, L3.2, U2.16 (VDDO_12)
unnamed: C4.1, C5.1, C6.1, L1.1, U2.15 (VDDO_034)
unnamed: C15.1, C16.1, C104.1, L4.2, U2.3 (VDD_REF)
unnamed: C9.1, C10.1, C17.1, L2.2, U2.24 (VDD_VCO)
REFSEL: R8.2, U2.4 (REFSEL); also elsewhere on the board
RST_N: U1.T15 (~RESET), U2.8 (PDN); also elsewhere on the board
RX_N: U1.V11 (SER_RX_N); also elsewhere on the board
RX_P: U1.U11 (SER_RX_P); also elsewhere on the board
SCL: U2.12 (SCL/GPIO3); also elsewhere on the board
SDA: U2.19 (SDA/GPIO2); also elsewhere on the board
TX_N: C21.1; also elsewhere on the board
TX_P: C20.1; also elsewhere on the board

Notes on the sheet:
Copyright (c) 2020-2024 Anton Kuzmin Licensed under CERN-OHL-P v2 https://github.com/gmm-7550/
